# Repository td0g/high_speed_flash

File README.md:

# high_speed_flash
This is the data repository for my microsecond strobe designs.  They are high-speed flashes used for photographing bullets or other projectiles or processes.  The entire project is open-source.

## MK1 - The Edgerton

The original strobe was designed to be simple to assemble and as affordable as possible.  Photographers, please be aware that some soldering skills are required.

## MK2 - The E2 Series

These are called a series because multiple submodels are planned.  Currently only the E2-A is complete.

The E2 series are very similar to the MK1 Edgerton, but have been designed with commercial production in mind.  You can build one yourself, but some more complicated processes are involved.  Additionally, the total cost is slightly higher.  The advantage is that the E2 series is smaller, more robust, and easier to use.

### Planned E2 Submodels:

E2-A | E2-K | E2-V
------------ | ------------- | -------------
Standard | High-powered 1-microsecond | Videographer
**Plans & specs available** | In development | In development
Strobe only | Strobe only | **120+ Watt Constant illumination mode**
Battery only | Battery only | **Battery OR external power supply**
**0.5 - 4 microsecond strobe** | 0.5 - 1 microsecond strobe | **0.5 - 4 microsecond strobe**
Standard LED Power | **Increased LED Power** | Standard LED Power
**Well-Established Safety Margin** | LED's more likely to fail | **Well-Established Safety Margin**

## Comparison

If you are trying to decide which design to use, have a look through this comparison.  Only the E2-A submodel is compared as it is most similar to the original Edgerton.

MK1 Edgerton | MK2 E2-A
------------ | -------------
**Same Performance** | **Same Performance**
**Affordable** | About 30% more expensive
**Relatively simple to assemble** (3D printer, soldering skills, Through-Hole Components) | Slightly more difficult (Aluminum milling / drilling, better cable management required, Surface-Mount Components)
Reliable | **Reliable PLUS**
8x AA batteries | **4x AA batteries**
Battery compartment difficult to access | **Easy to use battery compartment**
Cheap display | **Attractive, intuitive display**
Larger | **Smaller**
Single strobes only | **Multi-strobe capable**

## Research & Testing
The most valuable part of this project is the research and testing.  Many LED's have been destructively tested to find their limitations.  I plan to upload all of my testing data to this repository and encourage others to share any testing performed as well.

## License

Documentation is licensed under a [Creative Commons Attribution 4.0 International License](https://creativecommons.org/licenses/by/4.0/)

Software is licensed under a [GNU GPL v3 License](https://www.gnu.org/licenses/gpl-3.0.txt)

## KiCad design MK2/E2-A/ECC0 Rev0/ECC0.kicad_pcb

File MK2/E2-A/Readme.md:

# The MK2!

Building on the original Edgerton design, the E2-A is a high-speed flash used for photographing bullets or other projectiles.  The project is open-source.  Please see https://td0g.ca/2020/06/29/e2-a-the-high-speed-led-strobe-mk-2/ for more information.

## Building Your Flash
Please download and follow the [Assembly Manual](https://github.com/td0g/high_speed_flash/raw/master/MK2/E2-A/E2-A%20Assembly%20Manual.pdf).  This detailed manual should answer most of your questions.  Please contact me at tyler@td0g.ca if you find any errors or inconsistencies, or simply have questions!

The **EMCB1** main control board is slightly different than the one on the original Edgerton.  I plan to manufacture a few and make them available for sale.  You can also manufacture your own using the documentation in this repository!

The **ECC0** high-voltage boost converter is my own design.  Just like the EMCB1, you may build your own or contact me to purchase one.  Note that the ECC0 may eventually be updated to be compatible with the Edgerton design, but for now the maximum input voltage is 6 Volts.

The firmware has been tested and will make setup quick and easy.  Please flash it to your microcontroller using the Arduino IDE.  Before turning on your flash, please review the User's Manual.

## Files

**Assembly Manual** - The best way to build the flash

**GERBER's** - All the files you need to send to a board house if you want to have the control board built

**BOM** - Itemized list of all materials needed to manufacture the E2-A

**Firmware** - Upload using the Arduino IDE

**STL** - 3D print files

**Mechanical Drawings** - Drawings for manufacturing the aluminum faceplate

## License

Documentation is licensed under a [Creative Commons Attribution 4.0 International License](https://creativecommons.org/licenses/by/4.0/)

Software is licensed under a [GNU GPL v3 License](https://www.gnu.org/licenses/gpl-3.0.txt)

## Roadmap

### Rev 0

COMPLETE

### Rev 1

Finish this readme

Assembly Manual - complete and upload

Back_Cover.STL - redesign external trigger jack housing

EMCB1 - Some components are placed too closely, will need to increase board width by a couple mm

Operator's Manual - update

### Rev 2

Adding third PCB to design: EIB0.  This board will be mounted near the encoder and display.  It will host the 5V and 12.8V regulator.  The 12.8V regulator will be an SX1308-based boost converter, no longer an off-the-shelf converter.  The board will be connected to the EMCB1 control board using an FFC ribbon, which will dramatically improve cable management.  Battery power will be supplied to the EMCB1 by 22-gauge wires so that the XL6005 and MIC3172 have ample current supply.

The EMCB1 board will be updated with a 'modelling lamp' function, based on the XL6005 boost converter SMPS.  Max power is ~10W, efficiency is ~60%.

The EMCB1 and ECC0 boards will be modified such that they can connect directly - no wires.  Fewer wires = fewer failure opportunities and more compact design

The film capacitors will be rotated slightly to improve spacing.

USB-C connector on case to power strobe (eg. Raspberry Pi 4 PSU).  Adding CH340 chip so that FTDI adapter isn't required for firmware updates - just use USB-C connection.  See https://github.com/sparkfun/Serial_Basic_Breakout-CH340C

INVESTIGATE: Modified version to use 18650 battery(s).  1x 18650 would run the strobe, 2x could run the XL6005 boost converter at a higher power than 4x AA batteries.

INVESTIGATE: Increasing maximum exposure time

INVESTIGATE: Replacing TC4452 gate driver with more powerful driver

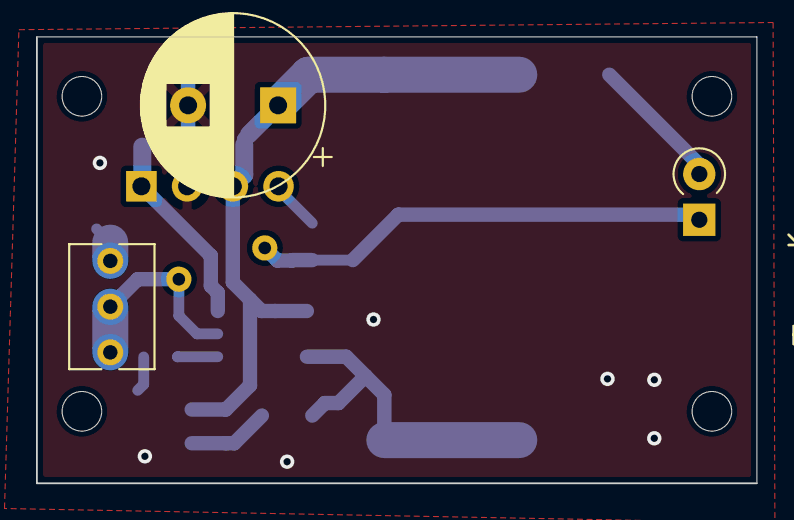
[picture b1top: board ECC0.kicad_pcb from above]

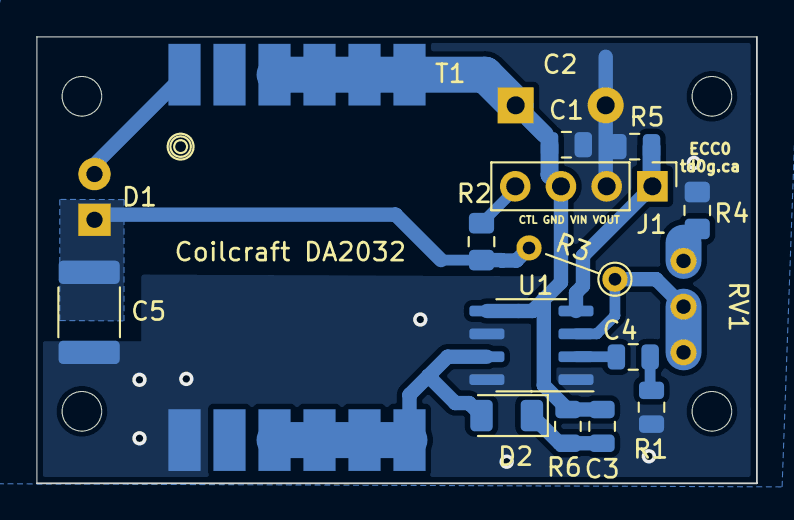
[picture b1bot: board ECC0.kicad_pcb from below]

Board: 2 copper layers, 40.0 x 24.8 mm, 21 parts (14 on the bottom side), 12 nets.

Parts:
C1: 10uF; C_0805_2012Metric
C2: 1000uF; CP_Radial_D10.0mm_P5.00mm
C3: C; C_0805_2012Metric
C4: 1uF; C_0805_2012Metric
C5: 1uF; C_1812_4532Metric_Pad1.30x3.40mm_HandSolder
D1: 2x 1N4148; D_A-405_P2.54mm_Vertical_KathodeUp
D2: D_Schottky; D_1206_3216Metric
H1, H2, H3, H4: MountingHole; MountingHole_2.2mm_M2
J1: Conn_01x04_Male; PinHeader_1x04_P2.54mm_Vertical
R1: 1K; R_0805_2012Metric
R2: 10K; R_0805_2012Metric_Pad1.15x1.40mm_HandSolder
R3: 470K; R_Axial_DIN0204_L3.6mm_D1.6mm_P5.08mm_Vertical
R4: 2.7K; R_0805_2012Metric_Pad1.15x1.40mm_HandSolder
R5: 470K; R_0805_2012Metric
R6: R; R_0805_2012Metric
RV1: 10K; Potentiometer_Bourns_3266Y_Vertical
T1: DA2032
U1: MIC3172; SOIC-8_3.9x4.9mm_P1.27mm

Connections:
+BATT: C1.2, C2.1, C3.1, J1.3, R6.1, T1.7, T1.8, T1.9, T1.10, U1.5
GND: C1.1, C2.2, C5.2, J1.2, R1.2, R4.1, R5.1, T1.1, U1.1, U1.6, U1.8
unnamed: C3.2, D2.1, R6.2
unnamed: C4.1, U1.2
unnamed: C4.2, R1.1
unnamed: C5.1, D1.1, R2.1, R3.2
unnamed: D1.2, T1.12
unnamed: D2.2, T1.3, T1.4, T1.5, T1.6, U1.7
unnamed: J1.1, R5.2, U1.4
unnamed: J1.4, R2.2
unnamed: R3.1, RV1.2, RV1.3, U1.3
unnamed: R4.2, RV1.1

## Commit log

2019-05-17 Rename RAY.ino to firmware/RAY.ino
2019-05-17 Rename TD0G_1637.cpp to firmware/TD0G_1637.cpp
2019-05-17 Rename TD0G_1637.h to firmware/TD0G_1637.h
2019-05-17 Rename _UIbackend.ino to firmware/_UIbackend.ino
2019-05-17 Rename _UIfrontEnd.ino to firmware/_UIfrontEnd.ino
2019-05-17 Rename _hardware.ino to firmware/_hardware.ino
2019-05-17 Rename _misc.ino to firmware/_misc.ino
2019-10-05 Corrected high-voltage booster connections
2019-10-16 Added 2019-10-14 R&D
2019-10-16 Added 2019-10-13 Testing
2019-11-04 New firmware
    New MAX_CAPACITOR_VOLTAGE
    Improved calibration setup
2020-05-06 Added Serial Communication section
2020-05-06 Added old test data
2020-07-07 Organized into MK1 and MK2 folders
2020-07-08 Moving firmware to MK1 folder
2020-08-06 New Test Data
2020-08-09 New Data
2020-08-23 E2 Development Testing Report
2020-08-30 Cleanup
2020-08-30 Variants placholders
2020-08-31 Update 2020-08-31
2020-08-31 Corrected mounting hole positions (86mm X spacing)
2020-09-01 Firmware 0.2.9
